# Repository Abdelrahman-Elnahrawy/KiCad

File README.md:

# KiCad Hardware Designs ⚡
**Electronic Schematic Capture & Multi-Layer PCB Design**

This repository serves as a portfolio and archive for my Printed Circuit Board (PCB) designs developed using **KiCad**. It includes everything from initial schematic capture to 3D modeling and production-ready manufacturing files.

---

## 🎯 Engineering Objectives
* **Schematic Capture:** Designing clean, hierarchical schematics with proper electrical rule checks (ERC).
* **PCB Layout:** High-speed routing, differential pairs, and optimized ground planes.
* **Component Management:** Creating custom footprints and 3D models for non-standard components.
* **Manufacturing Readiness:** Generating Gerber files, Drill files, and Bill of Materials (BOM) for fabrication (JLCPCB/PCBWay).

---

## 🏗️ Design Workflow
My design process follows industry standards for hardware development:

1. **Schematic Design:** Defining connections and selecting components.
2. **Footprint Assignment:** Linking symbols to physical footprints.
3. **Board Layout:** Defining board edges, placing components, and routing traces.
4. **Design Rule Check (DRC):** Ensuring the board meets manufacturing constraints.
5. **3D Visualization:** Verifying mechanical fit and component clearances.

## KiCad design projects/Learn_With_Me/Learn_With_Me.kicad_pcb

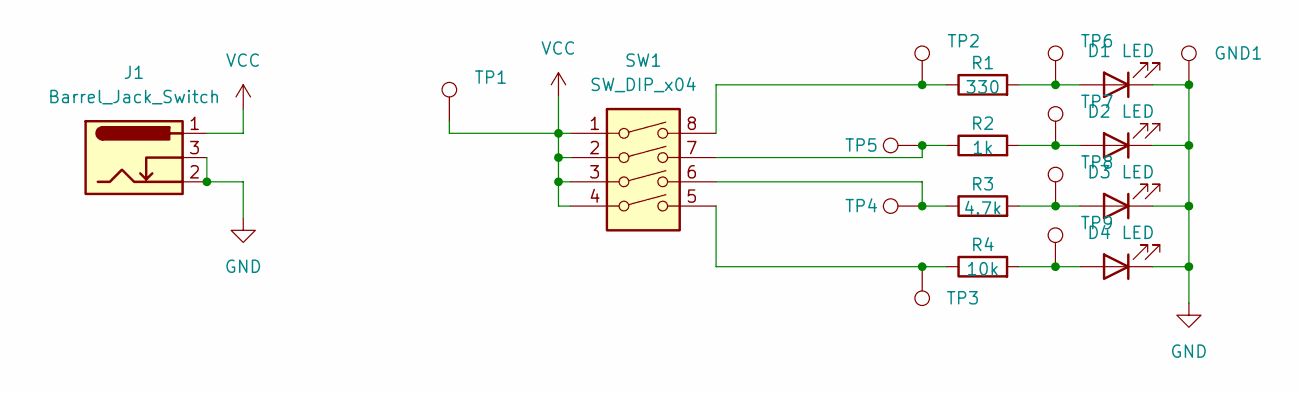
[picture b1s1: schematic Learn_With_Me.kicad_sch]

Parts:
D1, D2, D3, D4: LED; LED_D5.0mm
GND1: TestPoint; TestPoint_THTPad_D2.0mm_Drill1.0mm
J1: Barrel_Jack_Switch; BarrelJack_Wuerth_6941xx301002
R1: 330; R_Axial_DIN0204_L3.6mm_D1.6mm_P7.62mm_Horizontal
R2: 1k; R_Axial_DIN0204_L3.6mm_D1.6mm_P7.62mm_Horizontal
R3: 4.7k; R_Axial_DIN0204_L3.6mm_D1.6mm_P7.62mm_Horizontal
R4: 10k; R_Axial_DIN0204_L3.6mm_D1.6mm_P7.62mm_Horizontal
SW1: SW_DIP_x04; SW_DIP_SPSTx04_Slide_6.7x11.72mm_W7.62mm_P2.54mm_LowProfile
TP1, TP2, TP3, TP4, TP5, TP6, TP7, TP8, TP9: TestPoint; TestPoint_THTPad_D2.0mm_Drill1.0mm

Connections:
GND: D1.1 (K), D2.1 (K), D3.1 (K), D4.1 (K), GND1.1, J1.2, J1.3
unnamed: D1.2 (A), R1.2, TP6.1
unnamed: D2.2 (A), R2.2, TP7.1
unnamed: D3.2 (A), R3.2, TP8.1
unnamed: D4.2 (A), R4.2, TP9.1
unnamed: R1.1, SW1.8, TP2.1
unnamed: R2.1, SW1.7, TP5.1
unnamed: R3.1, SW1.6, TP4.1
unnamed: R4.1, SW1.5, TP3.1
VCC: J1.1, SW1.1, SW1.2, SW1.3, SW1.4, TP1.1

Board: 2 copper layers, 20 parts (0 on the bottom side), 10 nets, no tracks yet.

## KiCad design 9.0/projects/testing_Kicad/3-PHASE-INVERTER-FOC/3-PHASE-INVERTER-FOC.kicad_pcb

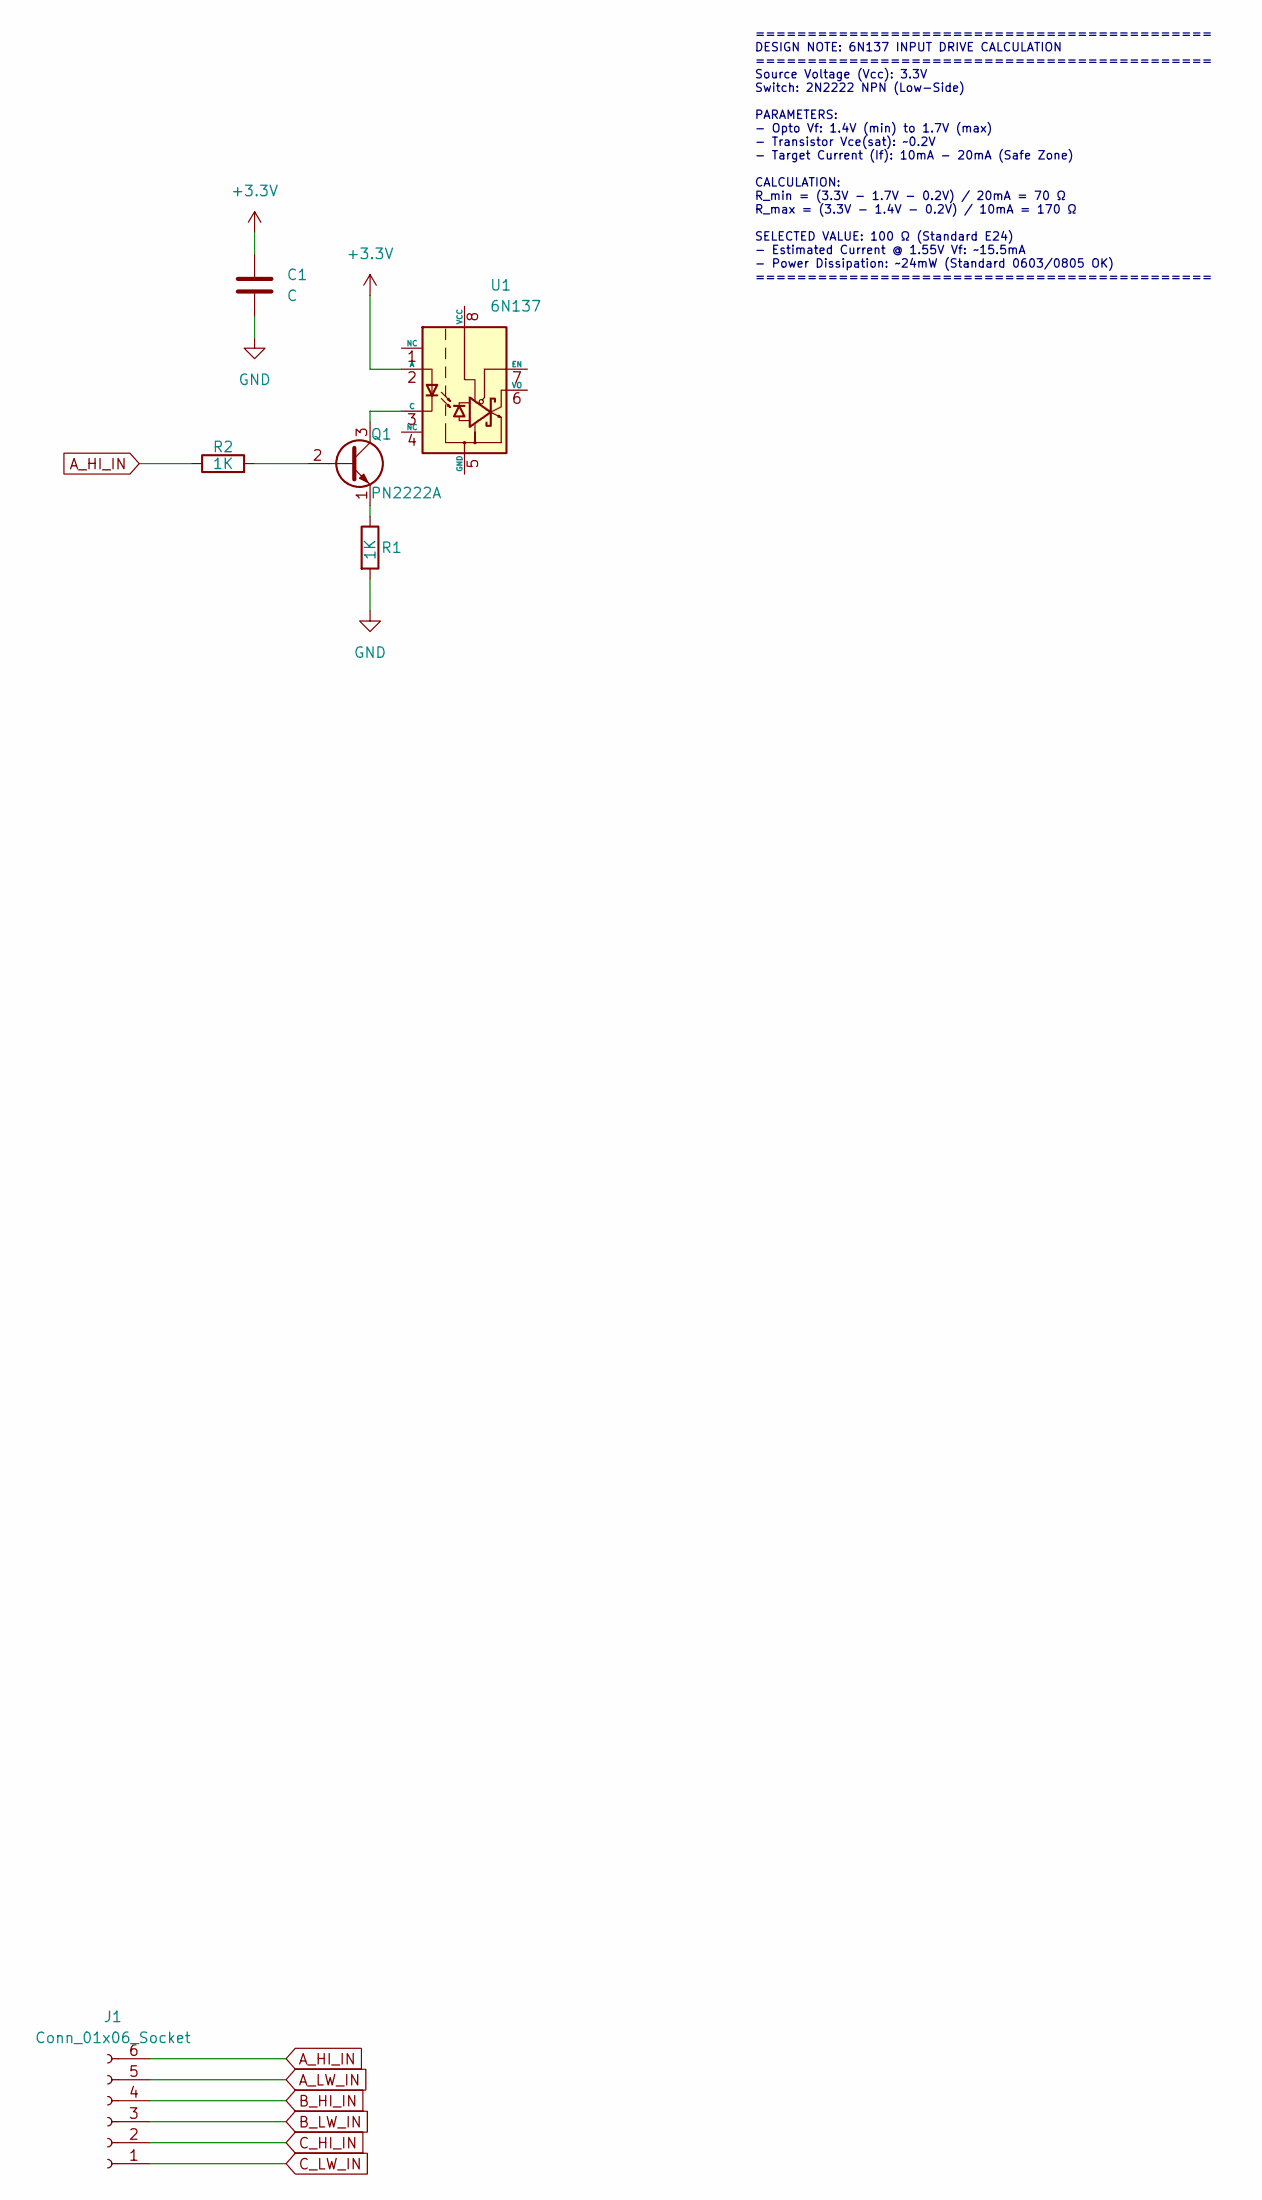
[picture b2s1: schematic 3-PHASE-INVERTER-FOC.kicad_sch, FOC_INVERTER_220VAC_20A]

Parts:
C1: C; C_Disc_D6.0mm_W2.5mm_P5.00mm
J1: Conn_01x06_Socket; PinHeader_1x06_P2.54mm_Vertical
Q1: PN2222A; TO-92_Inline
R1, R2: 1K; R_Axial_DIN0207_L6.3mm_D2.5mm_P10.16mm_Horizontal
U1: 6N137; DIP-8_W7.62mm

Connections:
+3.3V: C1.1, U1.2 (A)
A_HI_IN: J1.6, R2.1
A_LW_IN: J1.5
B_HI_IN: J1.4
B_LW_IN: J1.3
C_HI_IN: J1.2
C_LW_IN: J1.1
GND: C1.2, R1.2
unnamed: Q1.2 (B), R2.2
unnamed: Q1.3 (C), U1.3 (C)
unnamed: Q1.1 (E), R1.1

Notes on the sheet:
============================================ DESIGN NOTE: 6N137 INPUT DRIVE CALCULATION ============================================ Source Voltage (Vcc): 3.3V Switch: 2N2222 NPN (Low-Side) PARAMETERS: - Opto Vf: 1.4V (min) to 1.7V (max) - Transistor Vce(sat): ~0.2V - Target Current (If): 10mA - 20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

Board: 2 copper layers, 6 parts (0 on the bottom side), 6 nets, no tracks yet.

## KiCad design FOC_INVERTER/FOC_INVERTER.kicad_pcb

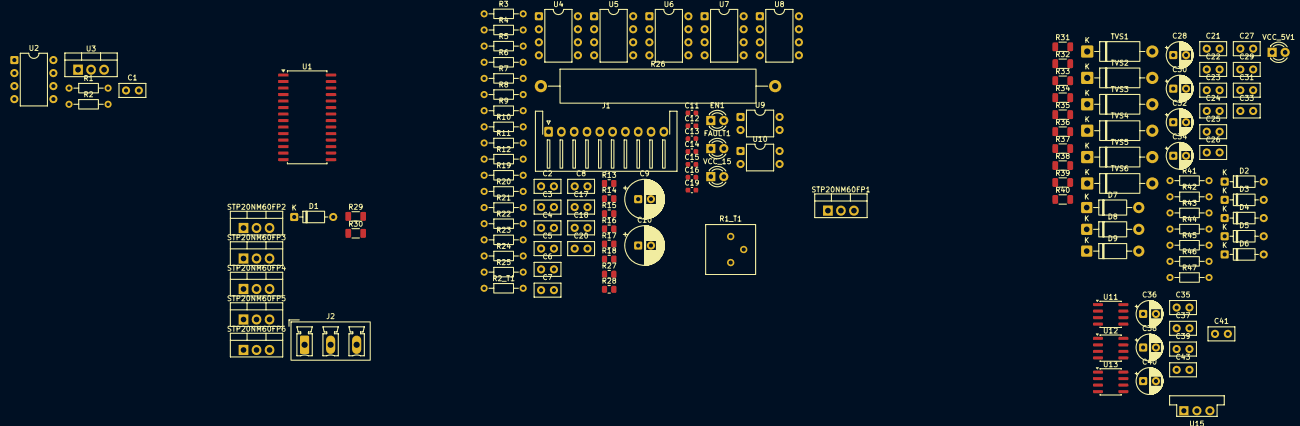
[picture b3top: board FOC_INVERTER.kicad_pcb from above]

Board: 2 copper layers, 132 parts (0 on the bottom side), 78 nets, no tracks yet.

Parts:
C1, C2, C4, C5, C6, C7, C8, C17, C18, C27, C29, C31, C33, C35, C37, C39: 100nF; C_Disc_D5.0mm_W2.5mm_P2.50mm
C3: C; C_Disc_D5.0mm_W2.5mm_P2.50mm
C9, C10: 100uF; CP_Radial_D7.5mm_P2.50mm
C11, C12, C13, C14, C15, C16: 100pF; C_0603_1608Metric
C19: 470pF; C_0603_1608Metric
C20: 200nF; C_Disc_D5.0mm_W2.5mm_P2.50mm
C21, C22, C23, C24, C25, C26: 1nF; C_Disc_D5.0mm_W2.5mm_P2.50mm
C28, C30, C32, C34: 10uF; CP_Radial_D5.0mm_P2.50mm
C36, C38, C40: 1uF; CP_Radial_D5.0mm_P2.50mm
C41: 2.2uF; C_Disc_D5.0mm_W2.5mm_P2.50mm
C43: 470pF; C_Disc_D5.0mm_W2.5mm_P2.50mm
D1, D2, D3, D4, D5, D6: 1N4148; D_DO-35_SOD27_P7.62mm_Horizontal
D7, D8, D9: UF4007; D_DO-41_SOD81_P10.16mm_Horizontal
EN1: BLUE - 3MM; LED_D3.0mm_IRBlack
FAULT1: RED - 3MM; LED_D3.0mm_IRBlack
J1: Conn_01x10_Pin; JST_XH_S10B-XH-A-1_1x10_P2.50mm_Horizontal
J2: Conn_01x03_Pin; PhoenixContact_MCV_1,5_3-G-5.08_1x03_P5.08mm_Vertical
R1, R2_T1, R4, R6, R8, R10, R12, R20, R22: 1K; R_Axial_DIN0204_L3.6mm_D1.6mm_P7.62mm_Horizontal
R1_T1: 10k Ω; Potentiometer_Bourns_3386P_Vertical
R2, R3, R5, R7, R9, R11, R19: 200; R_Axial_DIN0204_L3.6mm_D1.6mm_P7.62mm_Horizontal
R13, R14, R15, R16, R17, R18: 200; R_0805_2012Metric
R21: 1.3K; R_Axial_DIN0204_L3.6mm_D1.6mm_P7.62mm_Horizontal
R23, R24, R25, R47: 3KΩ; R_Axial_DIN0204_L3.6mm_D1.6mm_P7.62mm_Horizontal
R26: 0.11 Ω; R_Axial_Power_L38.0mm_W6.4mm_P45.72mm
R27: 1kΩ; R_0805_2012Metric
R28: 200KΩ; R_0805_2012Metric
R29, R31, R33, R35, R36, R37: 10Ω; R_1206_3216Metric
R30, R32, R34, R38, R39, R40: 17Ω; R_1206_3216Metric
R41, R42, R43, R44, R45, R46: 22Ω; R_Axial_DIN0204_L3.6mm_D1.6mm_P7.62mm_Horizontal
STP20NM60FP1, STP20NM60FP2, STP20NM60FP3, STP20NM60FP4, STP20NM60FP5, STP20NM60FP6: STP20NM60FP; TO-220-3_Vertical
TVS1, TVS2, TVS3, TVS4, TVS5, TVS6: P6KE18CA; D_DO-15_P12.70mm_Horizontal
U1: IR2136S; SOIC-28W_7.5x17.9mm_P1.27mm
U2, U4, U5, U6, U7, U8: 6N137; DIP-8_W7.62mm
U3: LM7805_TO220; TO-220-3_Vertical
U9, U10: PC817; DIP-4_W7.62mm
U11, U12, U13: ACS712xLCTR-20A; SOIC-8_3.9x4.9mm_P1.27mm
U15: MIC5219-3.3YM5; Converter_DCDC_Murata_OKI-78SR_Vertical
VCC_5V1: yellow - 3MM; LED_D3.0mm_IRBlack
VCC_15: GREEN - 3MM; LED_D3.0mm_IRBlack

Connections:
+5V: C1.1, C2.1, C3.1, C4.1, C5.1, C6.1, C8.1, C10.1, C36.1, C38.1, C40.1, R1.1, R4.1, R6.1, R8.1, R10.1, R12.1, R20.2, R22.2, U2.7 (EN), U2.8 (VCC), U3.3 (VO), U4.7 (EN), U4.8 (VCC), U5.7 (EN), U5.8 (VCC), U6.7 (EN), U6.8 (VCC), U7.7 (EN), U7.8 (VCC), U8.7 (EN), U8.8 (VCC), U11.8 (VCC), U12.8 (VCC), U13.8 (VCC), U15.1 (IN), U15.3 (EN), VCC_5V1.2 (A)
+15V: C7.1, C9.1, C33.2, C34.2, D7.2 (A), D8.2 (A), D9.2 (A), FAULT1.2 (A), R28.1, U1.1 (VCC), U3.1 (VI), VCC_15.2 (A)
+VDC: R41.1, R42.1, R46.1, STP20NM60FP4.2 (D), STP20NM60FP5.2 (D), STP20NM60FP6.2 (D)
/COM: C23.2, C24.2, C25.2, C33.1, C34.1, R1_T1.2, R26.2, STP20NM60FP1.3 (S), STP20NM60FP2.3 (S), STP20NM60FP3.3 (S), TVS1.2, TVS2.2, TVS5.2, U1.13 (COM)
/CON_A: J2.3, U11.3 (IP-), U11.4 (IP-)
/CON_B: J2.2, U12.3 (IP-), U12.4 (IP-)
/CON_C: J2.1, U13.3 (IP-), U13.4 (IP-)
/EN: C17.1, EN1.2 (A), R20.1, U1.10 (EN), U10.4
/EN_MCU: J1.3, R19.1
/FAULT: R21.1, R23.1, U1.8 (~FAULT)
/FAULT_MCU: C18.1, J1.1, R22.1, U9.4
/HIN1: R1.2, R13.1, U2.6 (VO)
/HIN2: R6.2, R14.1, U5.6 (VO)
/HIN3: R10.2, R15.1, U7.6 (VO)
/HO1: D6.2 (A), R40.2, STP20NM60FP4.1 (G), TVS6.1
/HO2: D5.2 (A), R39.2, STP20NM60FP5.1 (G), TVS4.1
/HO3: D4.2 (A), R38.2, STP20NM60FP6.1 (G), TVS3.1
/ITRIP: C19.1, R1_T1.1, R2_T1.2, R27.1
/LIN1: R4.2, R16.1, U4.6 (VO)
/LIN2: R8.2, R17.1, U6.6 (VO)
/LIN3: R12.2, R18.1, U8.6 (VO)
/LO1: D1.2 (A), R30.2, STP20NM60FP1.1 (G), TVS5.1
/LO2: D2.2 (A), R32.2, STP20NM60FP2.1 (G), TVS1.1
/LO3: D3.2 (A), R34.2, STP20NM60FP3.1 (G), TVS2.1
/OUT_A: C26.2, C31.2, C32.2, R45.1, STP20NM60FP1.2 (D), STP20NM60FP4.3 (S), TVS6.2, U1.26 (VS1), U11.1 (IP+), U11.2 (IP+)
/OUT_B: C21.2, C29.2, C30.2, R44.1, STP20NM60FP2.2 (D), STP20NM60FP5.3 (S), TVS4.2, U1.22 (VS2), U12.1 (IP+), U12.2 (IP+)
/OUT_C: C22.2, C27.2, C28.2, R43.1, STP20NM60FP3.2 (D), STP20NM60FP6.3 (S), TVS3.2, U1.18 (VS3), U13.1 (IP+), U13.2 (IP+)
/PWM_U_H: J1.4, R2.1
/PWM_U_L: J1.7, R3.1
/PWM_V_H: J1.5, R5.1
/PWM_V_L: J1.8, R7.1
/PWM_W_H: J1.6, R9.1
/RCIN: C20.1, R28.2, U1.11 (RCIN)
/VB1: C31.1, C32.1, D8.1 (K), U1.28 (VB1)
/VB2: C29.1, C30.1, D7.1 (K), U1.24 (VB2)
/VB3: C27.1, C28.1, D9.1 (K), U1.20 (VB3)
GND: C1.2, C2.2, C3.2, C4.2, C5.2, C6.2, C7.2, C8.2, C9.2, C10.2, C11.2, C12.2, C13.2, C14.2, C15.2, C16.2, C17.2, C18.2, C19.2, C20.2, C41.2, C43.2, R2_T1.1, R24.1, R25.1, R26.1, R47.1, U1.12 (VSS), U2.5 (GND), U3.2 (GND), U4.5 (GND), U5.5 (GND), U6.5 (GND), U7.5 (GND), U8.5 (GND), U9.3, U10.3, U15.2 (GND)
GNDD: C35.2, C36.2, C37.2, C38.2, C39.2, C40.2, J1.10, U2.3 (C), U4.3 (C), U5.3 (C), U6.3 (C), U7.3 (C), U8.3 (C), U9.2, U10.2, U11.5 (GND), U12.5 (GND), U13.5 (GND)
unnamed: C21.1, R41.2
unnamed: C22.1, R42.2
unnamed: C23.1, R43.2
unnamed: C24.1, R44.2
unnamed: C25.1, R45.2
unnamed: C26.1, R46.2
unnamed: D1.1 (K), R29.2
unnamed: D2.1 (K), R31.2
unnamed: D3.1 (K), R33.2
unnamed: D4.1 (K), R35.2
unnamed: D5.1 (K), R36.2
unnamed: D6.1 (K), R37.2
unnamed: EN1.1 (K), R24.2
unnamed: FAULT1.1 (K), R23.2
unnamed: R19.2, U10.1
unnamed: R21.2, U9.1
unnamed: R37.1, R40.1, U1.27 (HO1)
unnamed: R36.1, R39.1, U1.23 (HO2)
unnamed: R35.1, R38.1, U1.19 (HO3)
unnamed: R27.2, U1.9 (ITRIP)
unnamed: R29.1, R30.1, U1.16 (LO1)
unnamed: R31.1, R32.1, U1.15 (LO2)
unnamed: R33.1, R34.1, U1.14 (LO3)
unnamed: C16.1, R13.2, U1.2 (~HIN1)
unnamed: C15.1, R14.2, U1.3 (~HIN2)
unnamed: C14.1, R15.2, U1.4 (~HIN3)
unnamed: C13.1, R16.2, U1.5 (~LIN1)
unnamed: C12.1, R17.2, U1.6 (~LIN2)
unnamed: C11.1, R18.2, U1.7 (~LIN3)
unnamed: R2.2, U2.2 (A)
unnamed: R3.2, U4.2 (A)
unnamed: R5.2, U5.2 (A)
unnamed: R7.2, U6.2 (A)
unnamed: R9.2, U7.2 (A)
unnamed: R11.2, U8.2 (A)
unnamed: C35.1, U11.6 (FILTER)
unnamed: C37.1, U12.6 (FILTER)
unnamed: C39.1, U13.6 (FILTER)
unnamed: R47.2, VCC_5V1.1 (K)
unnamed: R25.2, VCC_15.1 (K)

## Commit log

2024-10-24 testing kicad
2026-01-02 Create LICENSE
2026-01-15 foc schematic semi done
2026-01-15 LAST
2026-01-17 schematic_done_rev_1.1
2026-03-28 partially finished Ohm's Law circuit
2026-04-14 Updating the Kicad repo to include everything
2026-04-14 removing dumb files
2026-04-14 adding projects as files not as reps
2026-04-14 add projects as a folder instead of a sperate repo
2026-04-14 removing project backup

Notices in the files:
README.md:
License: GNU-3.0
